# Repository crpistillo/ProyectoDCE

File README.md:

# ProyectoDCE

Los archivos correspondientes a la Primera entrega: TP1 - Etapa de control se encuentran en el directorio *PROYECTO_ETAPA_CONTROL*

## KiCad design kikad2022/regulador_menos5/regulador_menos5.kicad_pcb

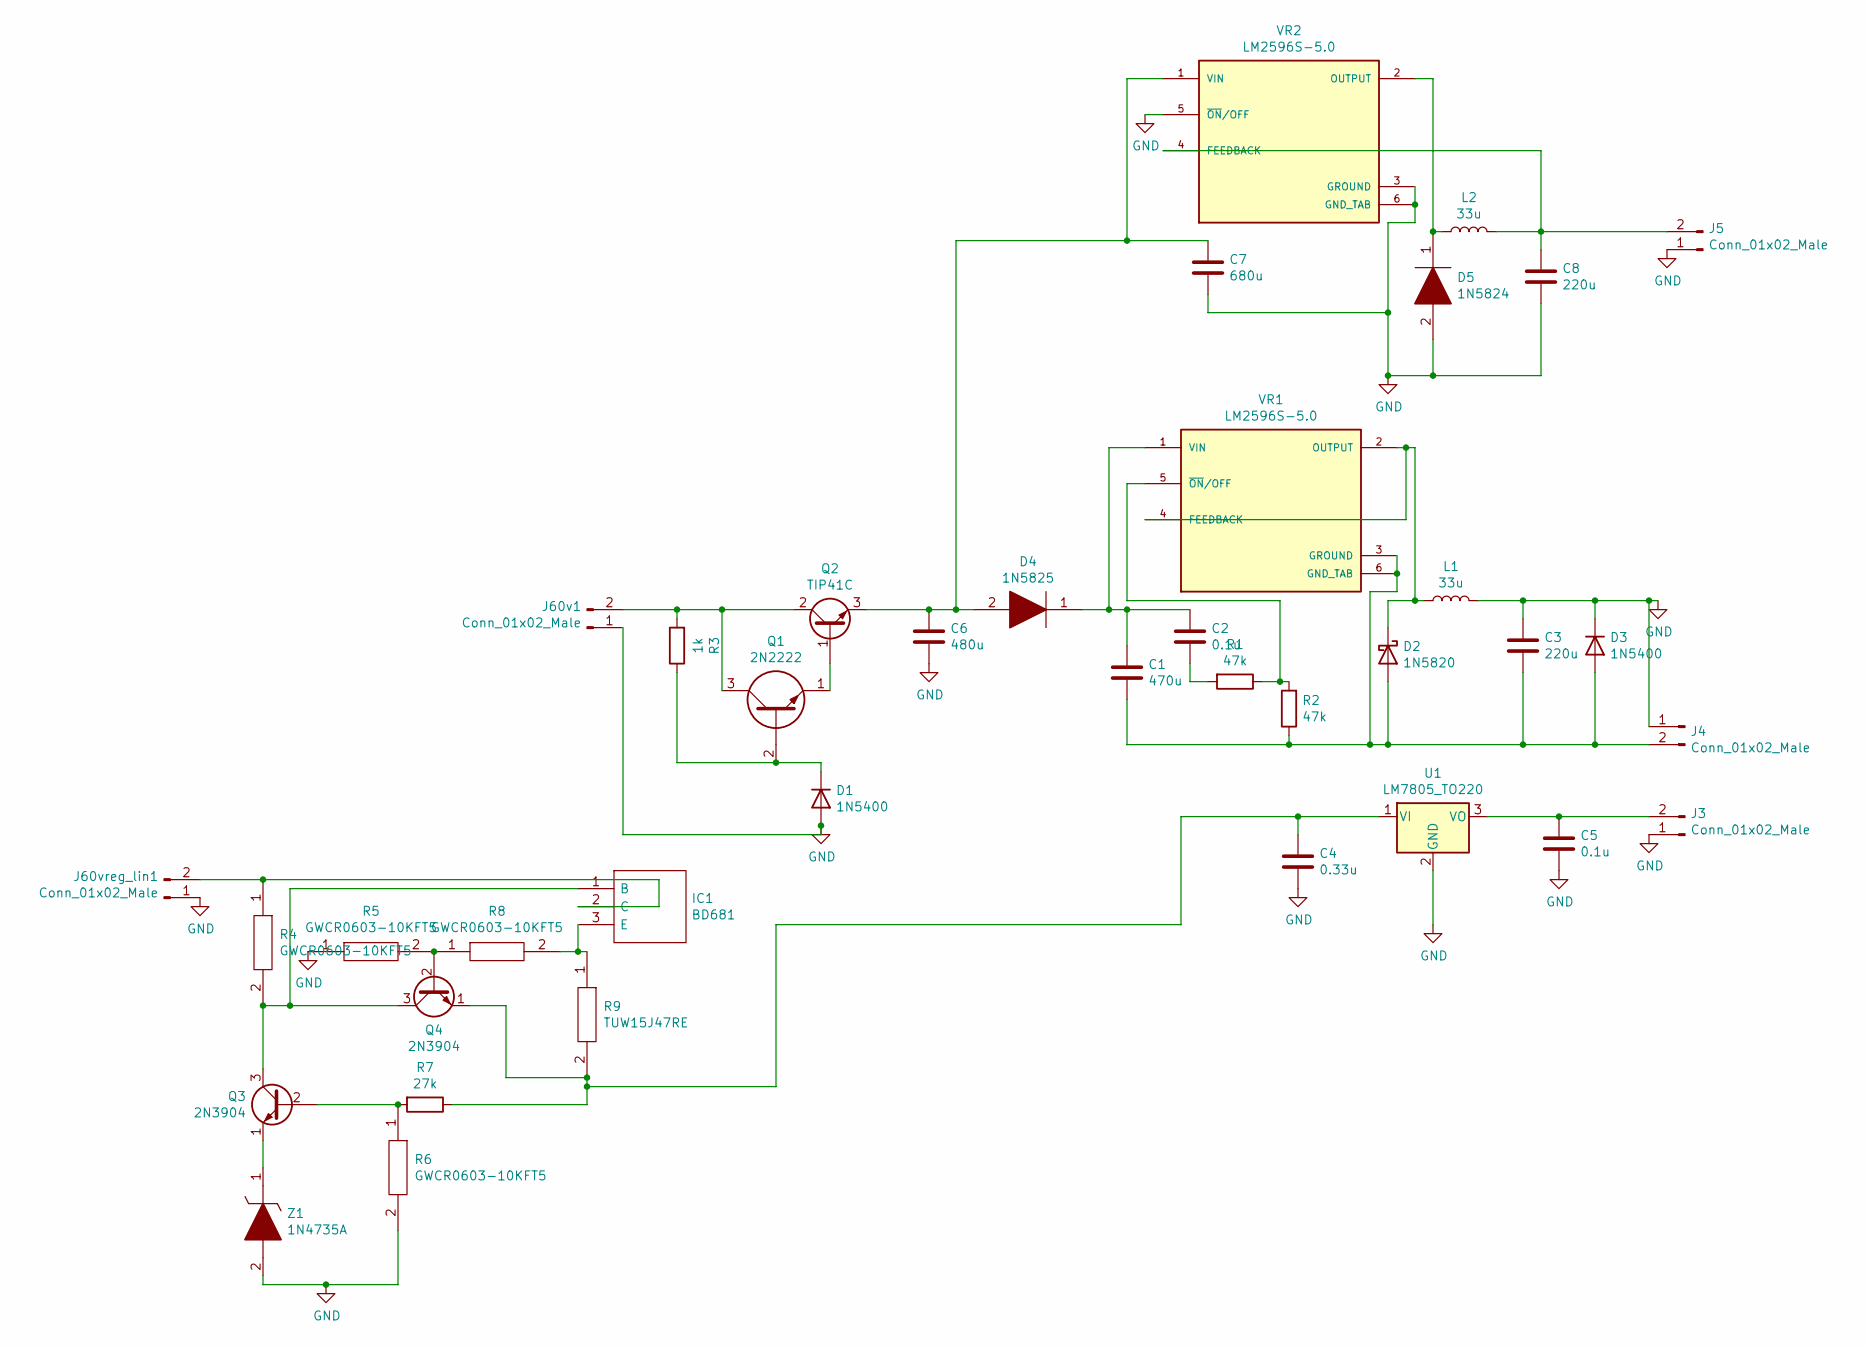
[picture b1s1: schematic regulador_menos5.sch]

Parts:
C1: 470u; CAPC2012X100N
C2, C5: 0.1u; CAPC2012X100N
C3, C8: 220u; CAPC2012X100N
C4: 0.33u; CAPC2012X100N
C6: 480u; CAPC2012X100N
C7: 680u; CAPC2012X100N
D1, D3: 1N5400; D_DO-201AD_P15.24mm_Horizontal
D2: 1N5820; D_DO-201AD_P15.24mm_Horizontal
D4: 1N5825; 1N5824; Manufacturer_Part_Number 1N5825; Mouser Part Number 494-1N5825
D5: 1N5824; Manufacturer_Part_Number 1N5824; Mouser Part Number 494-1N5824
IC1: BD681; TO254P290X760X1320-3P; Manufacturer_Part_Number BD681; Mouser Part Number 511-BD681
J3, J4, J5, J60v1, J60vreg_lin1: Conn_01x02_Male; Molex_KK-254_AE-6410-02A_1x02_P2.54mm_Vertical
L1, L2: 33u; L_TDK_NLV32_3.2x2.5mm
Q1: 2N2222; Manufacturer_Part_Number 2N2222
Q2: TIP41C; TO-220-3_Vertical
Q3, Q4: 2N3904; TO-92_Inline
R1, R2: 47k; R_0603_1608Metric
R3: 1k; R_0603_1608Metric
R4, R5, R6, R8: GWCR0603-10KFT5; RESC1608X55N; Manufacturer_Part_Number GWCR0603-10KFT5
R7: 27k; RESC1608X55N
R9: TUW15J47RE; TUW15J27RE; Manufacturer_Part_Number TUW15J47RE; Mouser Part Number 588-TUW15J47RE
U1: LM7805_TO220; TO-220-3_Vertical
VR1, VR2: LM2596S-5.0; KTT0005B; PARTREV E
Z1: 1N4735A; DIOAD1413W86L463D238; Manufacturer_Part_Number 1N4735A; Mouser Part Number 512-1N4735A

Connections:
GND: C3.1, C4.2, C5.2, C6.2, C7.2, C8.2, D1.2 (A), D3.1 (K), D5.2, J3.1, J4.1, J5.1, J60v1.1, J60vreg_lin1.1, L1.2, R5.1, R6.2, U1.2 (GND), VR2.3 (GROUND), VR2.5 (~ON~/OFF), VR2.6 (GND_TAB), Z1.2
unnamed: C1.1, C2.1, D4.1, VR1.1 (VIN)
unnamed: C1.2, C3.2, D2.2 (A), D3.2 (A), J4.2, R2.1, VR1.3 (GROUND), VR1.6 (GND_TAB)
unnamed: C2.2, R1.2
unnamed: C4.1, Q4.1 (E), R7.1, R9.2, U1.1 (VI)
unnamed: C5.1, J3.2, U1.3 (VO)
unnamed: C6.1, C7.1, D4.2, Q2.3 (E), VR2.1 (VIN)
unnamed: C8.1, J5.2, L2.2, VR2.4 (FEEDBACK)
unnamed: D1.1 (K), Q1.2, R3.1
unnamed: D2.1 (K), L1.1, VR1.2 (OUTPUT), VR1.4 (FEEDBACK)
unnamed: D5.1, L2.1, VR2.2 (OUTPUT)
unnamed: IC1.1 (B), Q3.3 (C), Q4.3 (C), R4.2
unnamed: IC1.2 (C), J60vreg_lin1.2, R4.1
unnamed: IC1.3 (E), R8.2, R9.1
unnamed: J60v1.2, Q1.3, Q2.2 (C), R3.2
unnamed: Q1.1, Q2.1 (B)
unnamed: Q3.1 (E), Z1.1
unnamed: Q3.2 (B), R6.1, R7.2
unnamed: Q4.2 (B), R5.2, R8.1
unnamed: R1.1, R2.2, VR1.5 (~ON~/OFF)

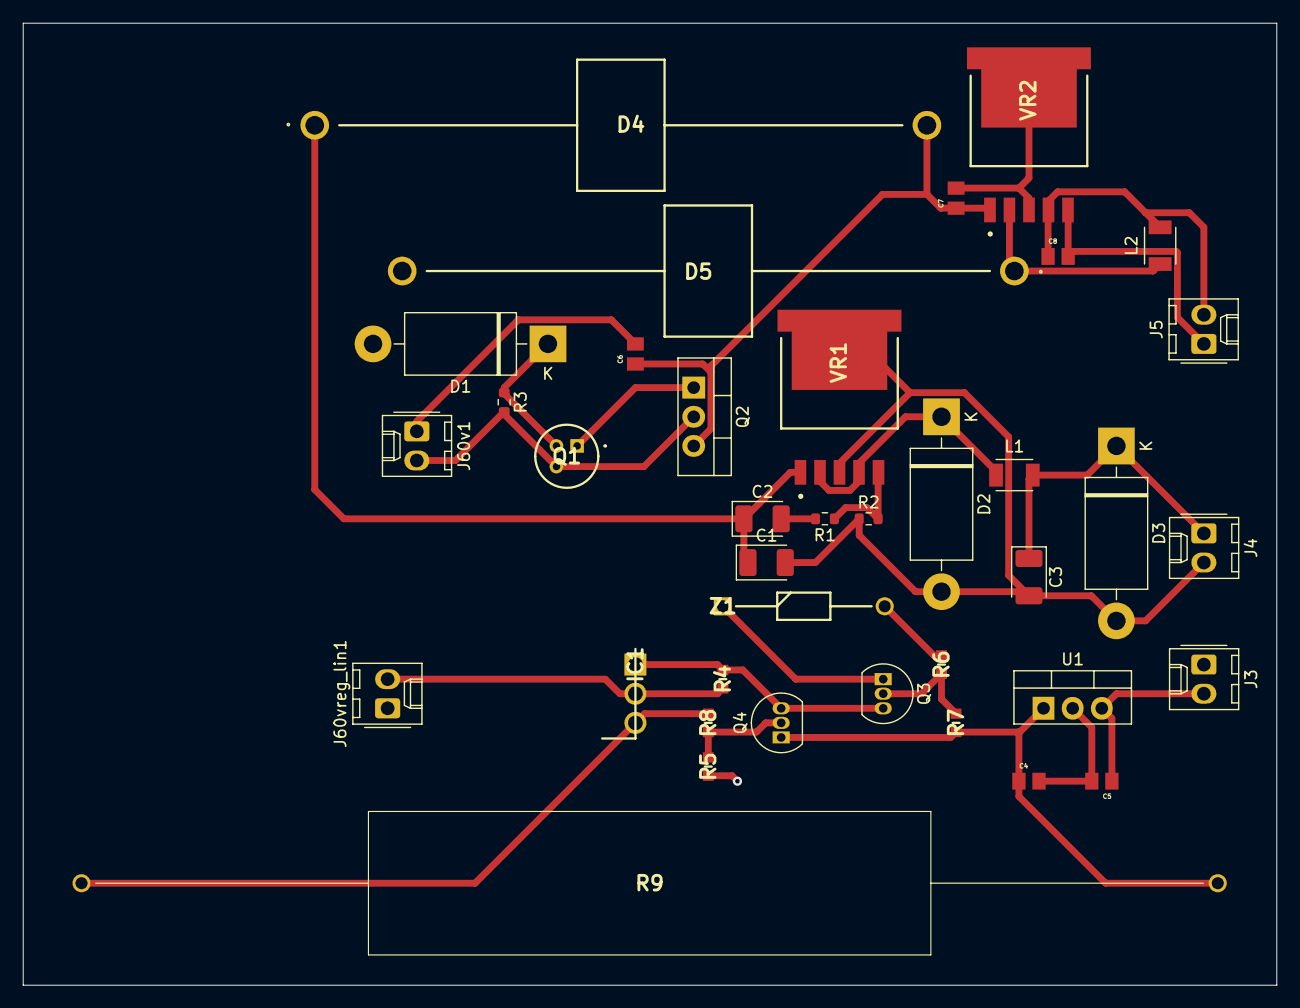
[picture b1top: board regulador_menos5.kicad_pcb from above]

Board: 2 copper layers, 109.2 x 83.8 mm, 38 parts (0 on the bottom side), 20 nets.

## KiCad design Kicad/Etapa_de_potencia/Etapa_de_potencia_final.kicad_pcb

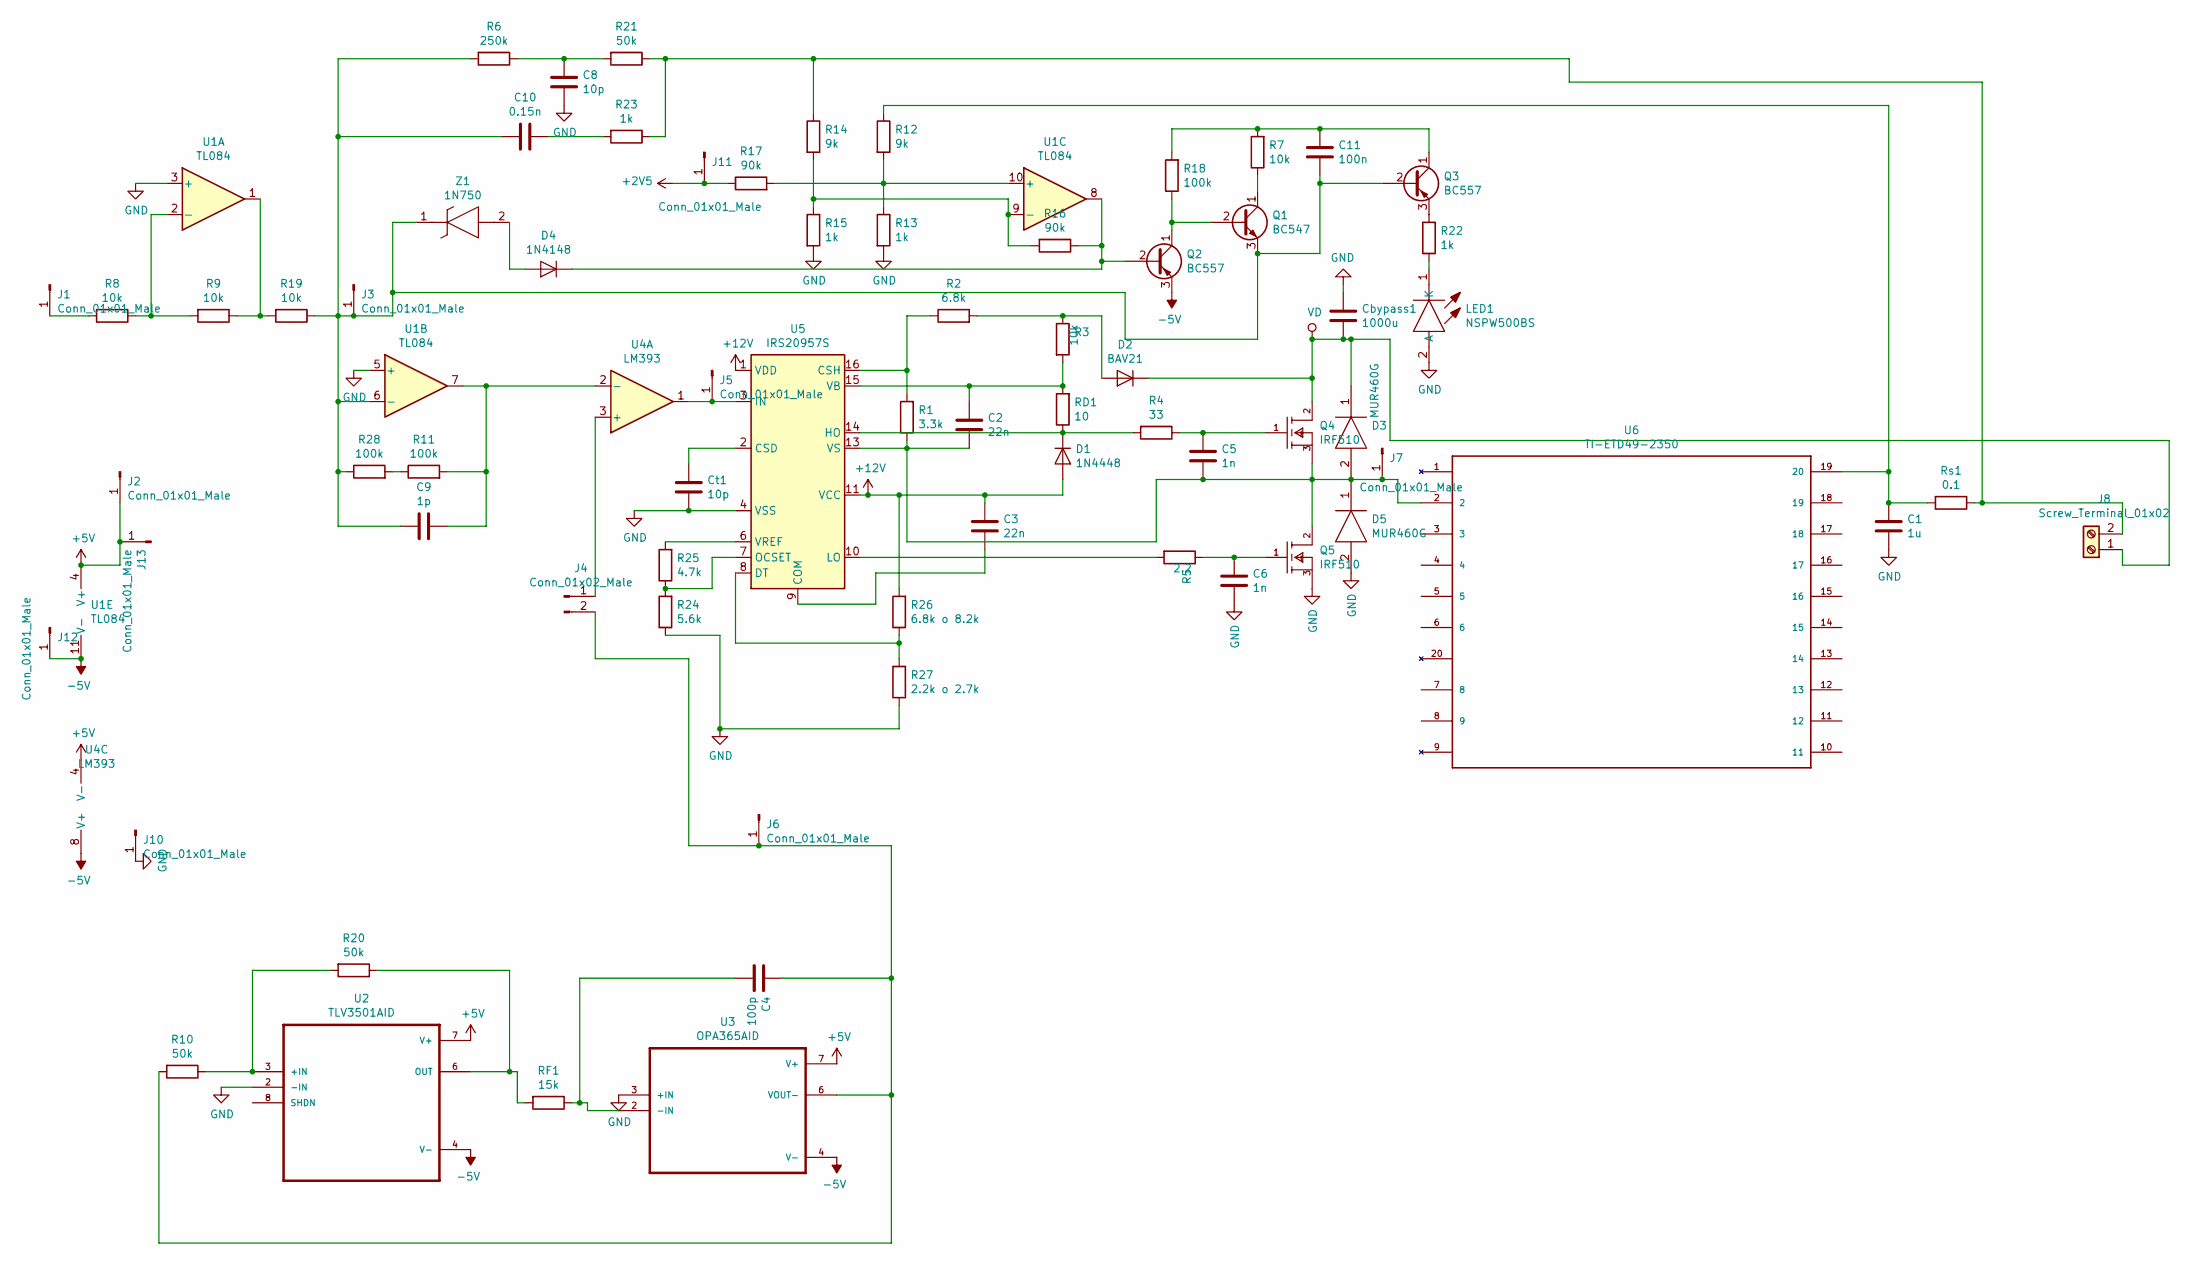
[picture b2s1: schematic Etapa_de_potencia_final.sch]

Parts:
C1: 1u; C_Radial_D5.0mm_H11.0mm_P2.00mm
C2, C3: 22n; C_1206_3216Metric
C4: 100p; C_1206_3216Metric
C5, C6: 1n; C_1206_3216Metric
C8: 10p; C_1206_3216Metric
C9: 1p; C_Disc_D8.0mm_W5.0mm_P5.00mm
C10: 0.15n; C_0805_2012Metric
C11: 100n; C_0603_1608Metric
Cbypass1: 1000u; C_Radial_D16.0mm_H25.0mm_P7.50mm
Ct1: 10p; C_1206_3216Metric
D1: 1N4448; D_DO-35_SOD27_P7.62mm_Horizontal
D2: BAV21; D_DO-35_SOD27_P7.62mm_Horizontal
D3, D5: MUR460G; DIOAD2860W130L840D505; Manufacturer_Part_Number MUR460G; Mouser Part Number 863-MUR460G
D4: 1N4148; D_DO-35_SOD27_P7.62mm_Horizontal
J1, J2, J3, J5, J6, J7, J10, J11, J12, J13: Conn_01x01_Male; PinHeader_1x01_P1.00mm_Vertical
J4: Conn_01x02_Male; PinHeader_1x02_P1.00mm_Vertical
J8: Screw_Terminal_01x02; TerminalBlock_bornier-2_P5.08mm
LED1: NSPW500BS; Manufacturer_Part_Number NSPW500BS
Q1: BC547; TO-92_Inline
Q2, Q3: BC557; TO-92_Inline
Q4, Q5: IRF510; Vishay-IRF510-0; mouser part number 844-IRF510; digikey description MOSFET N-CH 100V 5.6A TO-220AB
R1: 3.3k; R_0603_1608Metric
R2: 6.8k; R_0603_1608Metric
R3, R7, R8, R9, R19: 10k; R_0603_1608Metric
R4: 33; R_Axial_DIN0309_L9.0mm_D3.2mm_P2.54mm_Vertical
R5: 2.2; R_Axial_DIN0309_L9.0mm_D3.2mm_P2.54mm_Vertical
R6: 250k; R_0603_1608Metric
R10, R20, R21: 50k; R_0603_1608Metric
R11, R18, R28: 100k; R_0603_1608Metric
R12, R14: 9k; R_0603_1608Metric
R13, R15, R22, R23: 1k; R_0603_1608Metric
R16, R17: 90k; R_0603_1608Metric
R24: 5.6k; R_0603_1608Metric
R25: 4.7k; R_0603_1608Metric
R26: 6.8k o 8.2k; R_0603_1608Metric
R27: 2.2k o 2.7k; R_0603_1608Metric
RD1: 10; R_0603_1608Metric
RF1: 15k; R_0603_1608Metric
Rs1: 0.1; R_0603_1608Metric
U1: TL084; SOIC-14_3.9x8.7mm_P1.27mm
U2: TLV3501AID; SOIC127P599X175-8N
U3: OPA365AID; SOIC127P599X175-8N
U4: LM393; SOIC-8_3.9x4.9mm_P1.27mm
U5: IRS20957S; SOIC-16_3.9x9.9mm_P1.27mm
U6: TI-ETD49-2350; ETD49-K-H-20P
Z1: 1N750; DIOAD1256W56L444D203; Manufacturer_Part_Number 1N750; Mouser Part Number 494-1N750(DO-35)

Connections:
+2V5: J11.1, R17.1
+5V: J2.1, J13.1, U1.4 (V+), U2.7 (V+), U3.7 (V+), U4.4 (V-)
+12V: C3.2, D1.2 (A), R26.2, U5.1 (VDD), U5.11 (VCC)
-5V: J12.1, Q2.3 (E), U1.11 (V-), U2.4 (V-), U3.4 (V-), U4.8 (V+)
GND: C1.2, C6.2, C8.1, Cbypass1.2, Ct1.1, D5.2, J10.1, LED1.2 (A), Q5.3 (S), R13.2, R15.2, R24.1, R27.1, U1.3 (+), U1.5 (+), U2.2 (-IN), U3.3 (+IN), U5.4 (VSS)
unnamed: C1.1, R12.1, Rs1.2, U6.19 (20)
unnamed: C2.1, C5.2, D3.2, D5.1, J7.1, Q4.3 (S), Q5.2 (D), R1.1, U5.13 (VS), U6.2
unnamed: C2.2, R3.2, RD1.2, U5.15 (VB)
unnamed: C3.1, U5.9 (COM)
unnamed: C4.1, RF1.1, U3.2 (-IN)
unnamed: C4.2, J4.2, J6.1, R10.2, U3.6 (VOUT-)
unnamed: C5.1, Q4.1 (G), R4.1
unnamed: C6.1, Q5.1 (G), R5.1
unnamed: C8.2, R6.1, R21.2
unnamed: C9.1, R11.2, U1.7, U4.2 (-)
unnamed: C9.2, C10.1, C11.1, J3.1, Q1.3 (E), Q3.2 (B), R6.2, R19.1, R28.1, U1.6 (-), Z1.1
unnamed: C10.2, R23.2
unnamed: C11.2, Q3.1 (C), R7.2, R18.2
unnamed: Ct1.2, U5.2 (CSD)
unnamed: D1.1 (K), R4.2, RD1.1, U5.14 (HO)
unnamed: D2.2 (A), R2.2, R3.1
unnamed: D4.1 (K), Q2.2 (B), R16.1, U1.8
unnamed: D4.2 (A), Z1.2
unnamed: J1.1, R8.2
unnamed: J4.1, U4.3 (+)
unnamed: J5.1, U4.1, U5.3 (IN)
unnamed: J8.2, R14.1, R21.1, R23.1, Rs1.1
unnamed: LED1.1 (K), R22.1
unnamed: Q1.1 (C), R7.1
unnamed: Q1.2 (B), Q2.1 (C), R18.1
unnamed: Q3.3 (E), R22.2
unnamed: R1.2, R2.1, U5.16 (CSH)
unnamed: R5.2, U5.10 (LO)
unnamed: R8.1, R9.2, U1.2 (-)
unnamed: R10.1, R20.2, U2.3 (+IN)
unnamed: R11.1, R28.2
unnamed: R12.2, R13.1, R17.2, U1.10 (+)
unnamed: R14.2, R15.1, R16.2, U1.9 (-)
unnamed: R9.1, R19.2, U1.1
unnamed: R20.1, RF1.2, U2.6 (OUT)
unnamed: R24.2, R25.1, U5.7 (OCSET)
unnamed: R25.2, U5.6 (VREF)
unnamed: R26.1, R27.2, U5.8 (DT)
VD: Cbypass1.1, D2.1 (K), D3.1, J8.1, Q4.2 (D)

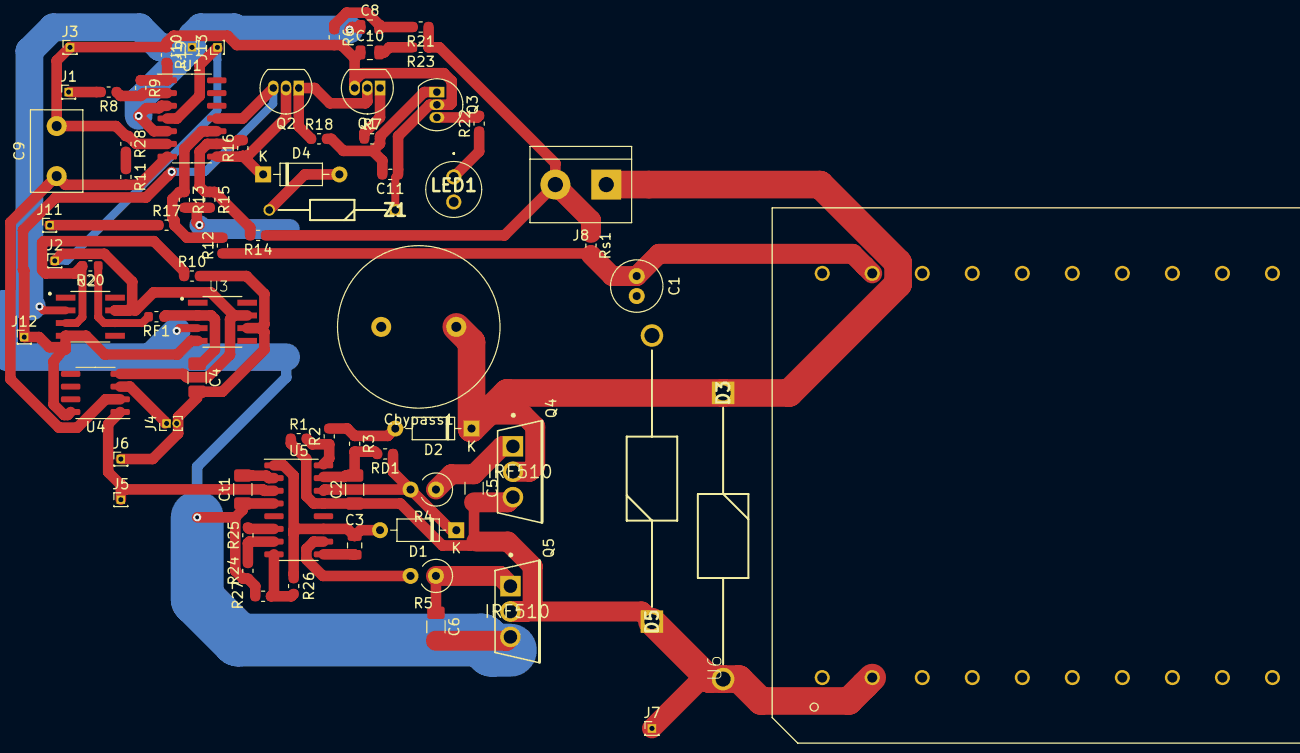
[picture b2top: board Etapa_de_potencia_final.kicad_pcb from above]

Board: 2 copper layers, 73 parts (0 on the bottom side), 44 nets.

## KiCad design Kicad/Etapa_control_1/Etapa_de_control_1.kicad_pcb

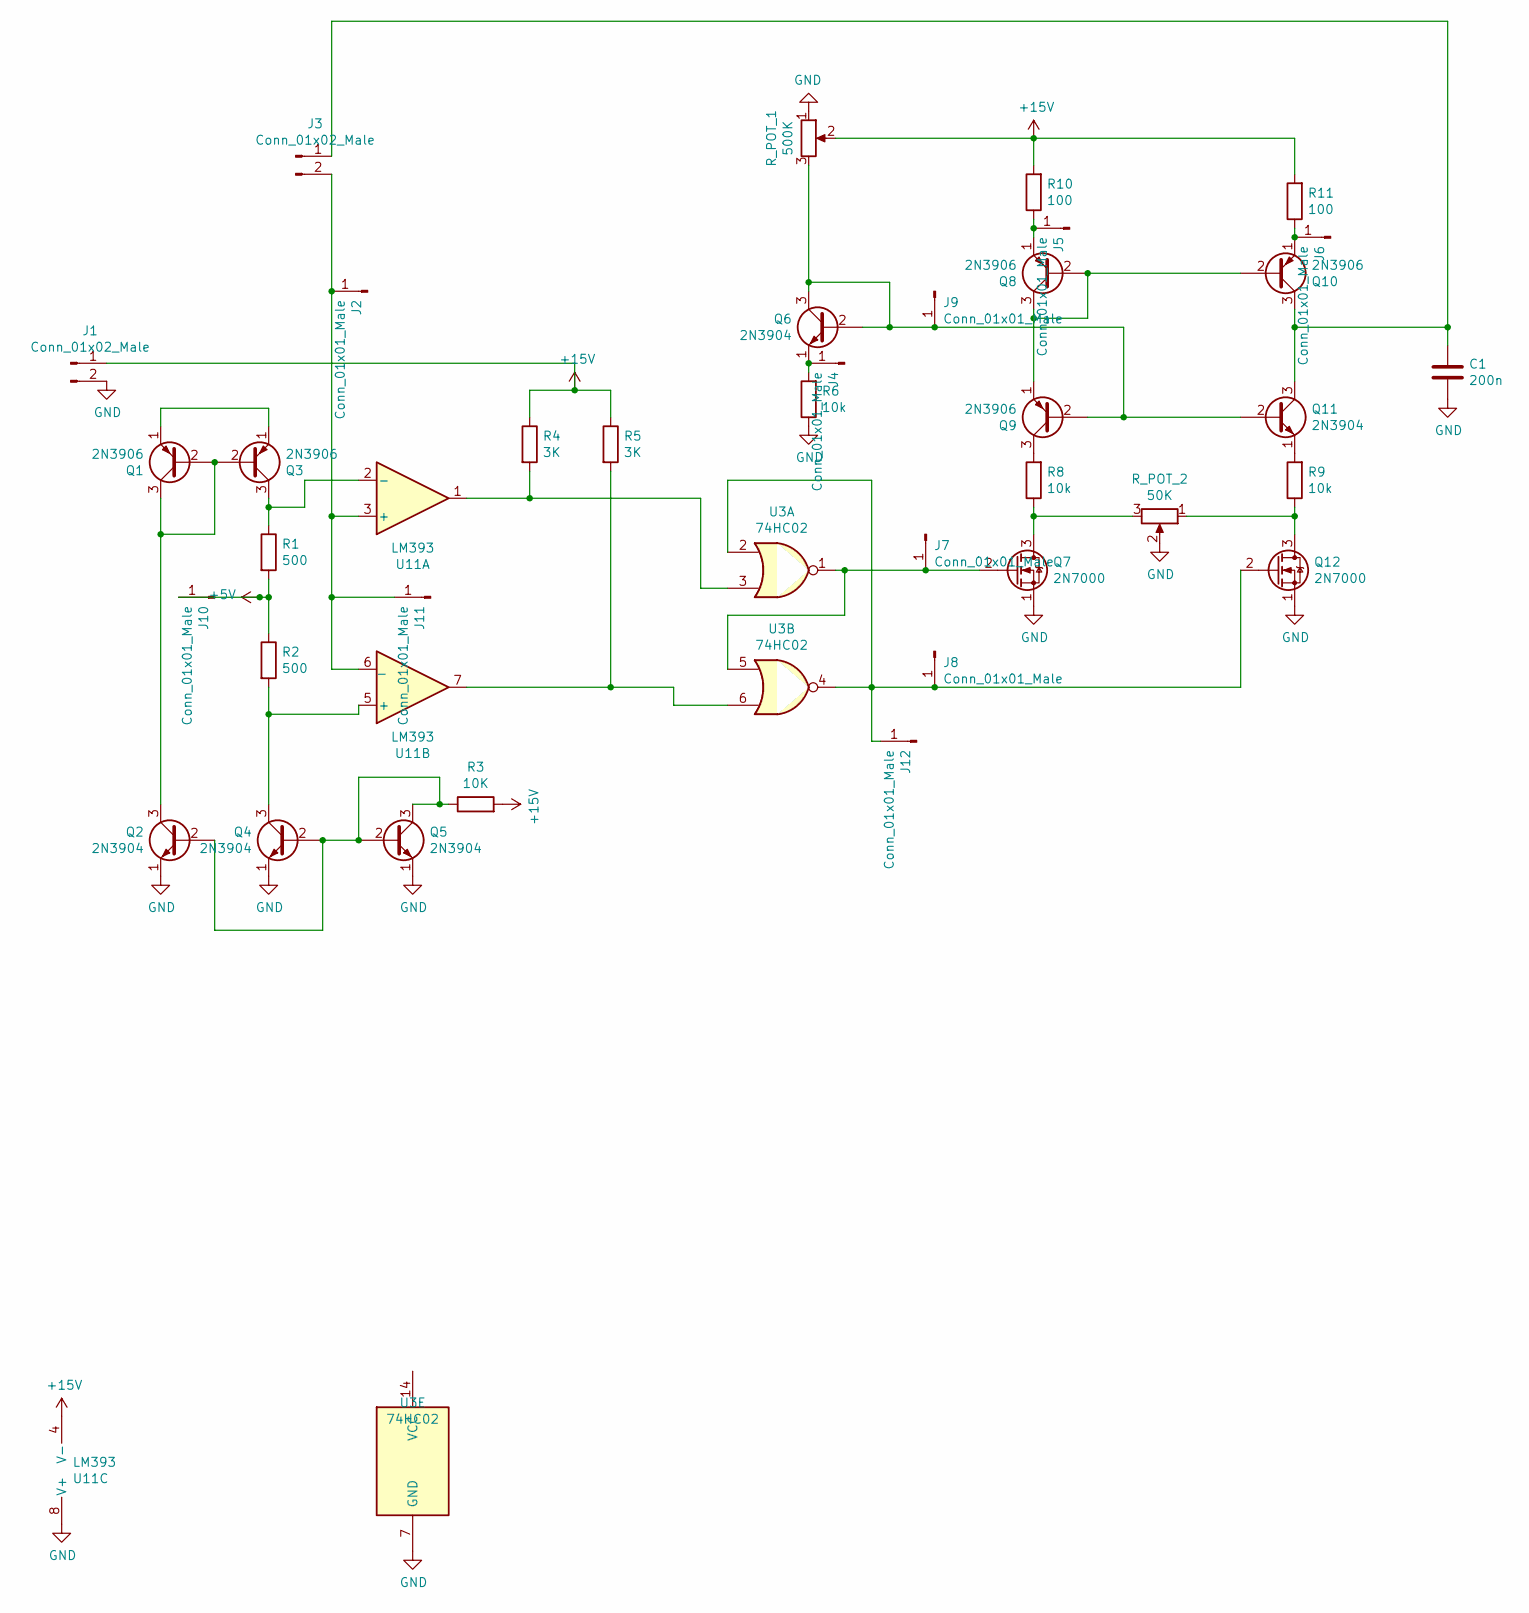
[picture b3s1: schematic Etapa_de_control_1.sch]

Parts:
C1: 200n; C_Disc_D3.8mm_W2.6mm_P2.50mm
J1, J3: Conn_01x02_Male; PinHeader_1x02_P1.00mm_Vertical
J2, J4, J5, J6, J7, J8, J9, J10, J11, J12: Conn_01x01_Male; PinHeader_1x01_P1.00mm_Vertical
Q1, Q3, Q8, Q9, Q10: 2N3906; TO-92_Inline
Q2, Q4, Q5, Q6, Q11: 2N3904; TO-92_Inline
Q7, Q12: 2N7000; TO-92_Inline
R1, R2: 500; R_0603_1608Metric
R3: 10K; R_0603_1608Metric
R4, R5: 3K; R_0603_1608Metric
R6, R8, R9: 10k; R_0603_1608Metric
R10, R11: 100; R_0603_1608Metric
R_POT_1: 500K; Potentiometer_Bourns_3296W_Vertical
R_POT_2: 50K; Potentiometer_Bourns_3296W_Vertical
U3: 74HC02; DIP-14_W7.62mm
U11: LM393; DIP-8_W7.62mm

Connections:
+5V: J10.1, R1.2, R2.1
+15V: J1.1, R3.2, R4.1, R5.1, R10.2, R11.2, R_POT_1.2, U11.4 (V-)
GND: C1.2, J1.2, Q2.1 (E), Q4.1 (E), Q5.1 (E), Q7.1 (S), Q12.1 (S), R6.1, R_POT_1.1, R_POT_2.2, U3.7 (GND), U11.8 (V+)
unnamed: C1.1, J3.1, Q10.3 (C), Q11.3 (C)
unnamed: J4.1, Q6.1 (E), R6.2
unnamed: J5.1, Q8.1 (E), R10.1
unnamed: J6.1, Q10.1 (E), R11.1
unnamed: J7.1, Q7.2 (G), U3.1, U3.5
unnamed: J9.1, Q6.2 (B), Q6.3 (C), Q9.2 (B), Q11.2 (B), R_POT_1.3
unnamed: J2.1, J3.2, J11.1, U11.3 (+), U11.6 (_)
unnamed: J8.1, J12.1, Q12.2 (G), U3.2, U3.4
unnamed: Q1.1 (E), Q3.1 (E)
unnamed: Q1.2 (B), Q1.3 (C), Q2.3 (C), Q3.2 (B)
unnamed: Q2.2 (B), Q4.2 (B), Q5.2 (B), Q5.3 (C), R3.1
unnamed: Q3.3 (C), R1.1, U11.2 (-)
unnamed: Q4.3 (C), R2.2, U11.5 (+)
unnamed: Q7.3 (D), R8.1, R_POT_2.3
unnamed: Q9.3 (C), R8.2
unnamed: Q8.2 (B), Q8.3 (C), Q9.1 (E), Q10.2 (B)
unnamed: Q11.1 (E), R9.2
unnamed: Q12.3 (D), R9.1, R_POT_2.1
unnamed: R4.2, U3.3, U11.1
unnamed: R5.2, U3.6, U11.7

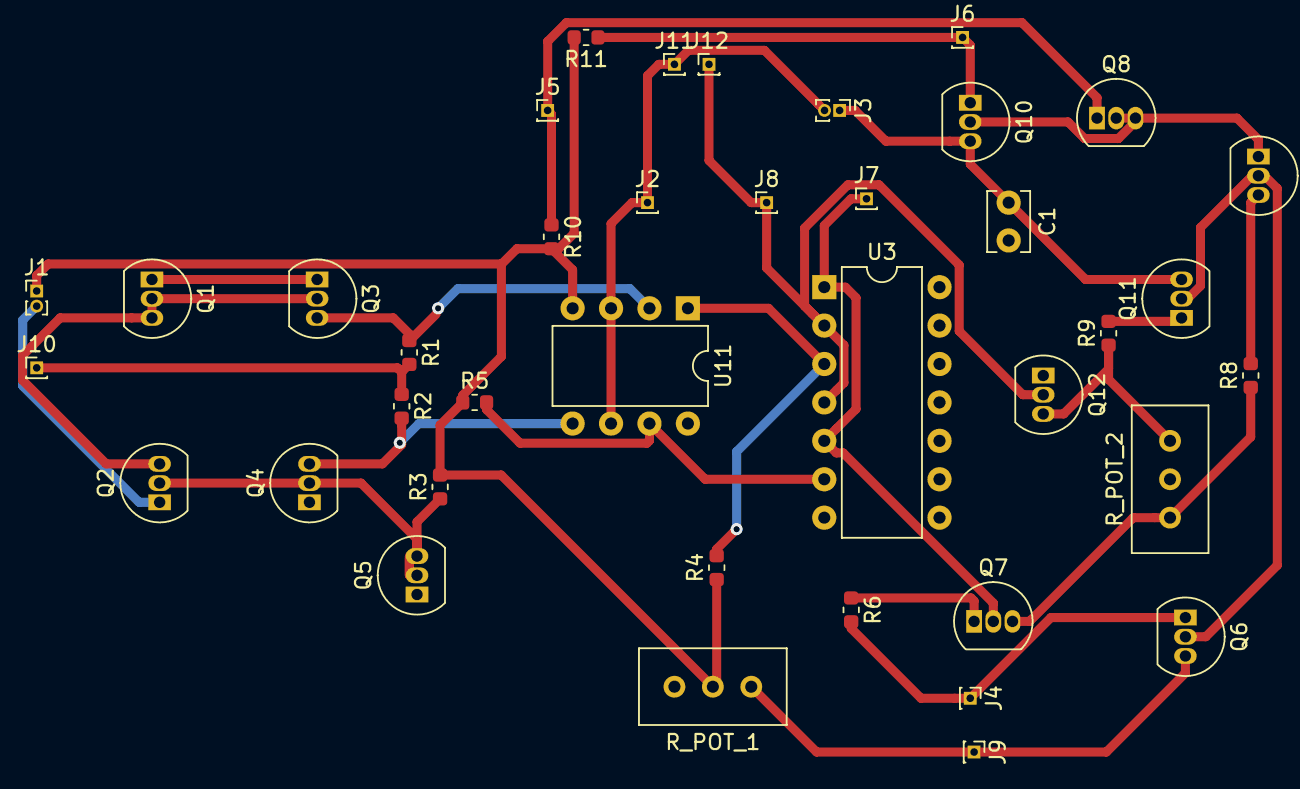
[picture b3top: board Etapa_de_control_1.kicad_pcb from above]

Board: 2 copper layers, 39 parts (0 on the bottom side), 23 nets.

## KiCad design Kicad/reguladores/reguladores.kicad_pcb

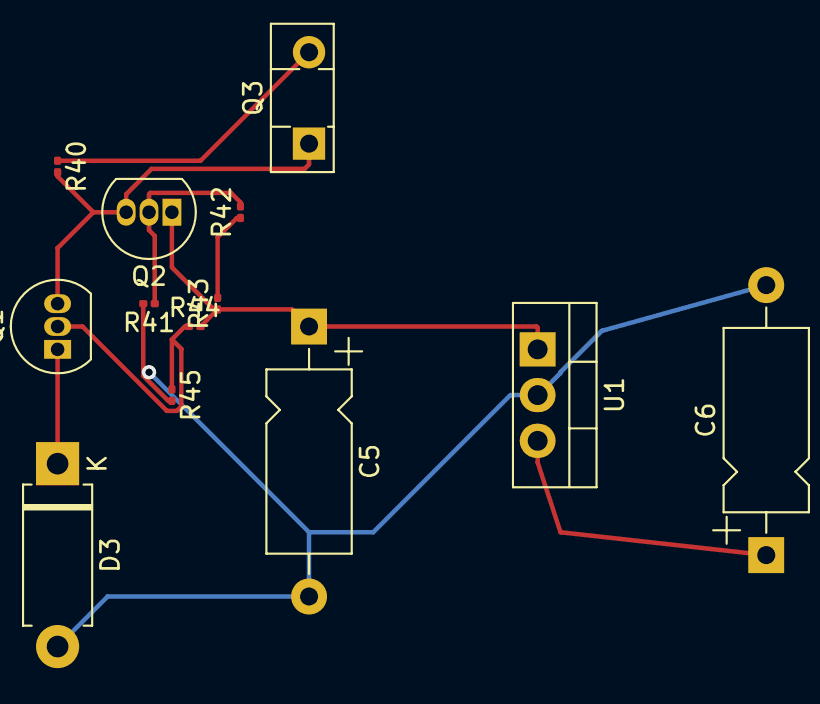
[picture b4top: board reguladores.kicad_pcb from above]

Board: 2 copper layers, 13 parts (0 on the bottom side), 9 nets.

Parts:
C5, C6: 100n; CP_Axial_L10.0mm_D4.5mm_P15.00mm_Horizontal
D3: 1N47xxA; D_DO-15_P10.16mm_Horizontal
Q1, Q2: 2N3904; TO-92_Inline
Q3: Q_NPN_Darlington_BCE; TO-126-2_Vertical
R40, R45: 10K; R_0201_0603Metric
R41, R42: 2K; R_0201_0603Metric
R43: 26; R_0201_0603Metric
R44: 27K; R_0201_0603Metric
U1: LM7815_TO220; TO-220-3_Vertical

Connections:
GND: C5.2, C6.2, D3.2, R41.2, R45.2, U1.2
unnamed: C5.1, Q2.1, R43.1, R44.2, U1.1
unnamed: C6.1, U1.3
unnamed: D3.1, Q1.1
unnamed: Q1.2, R44.1, R45.1
unnamed: Q1.3, Q2.3, Q3.1, R40.2
unnamed: Q2.2, R41.1, R42.2
unnamed: R42.1, R43.2
VCC: Q3.2, R40.1

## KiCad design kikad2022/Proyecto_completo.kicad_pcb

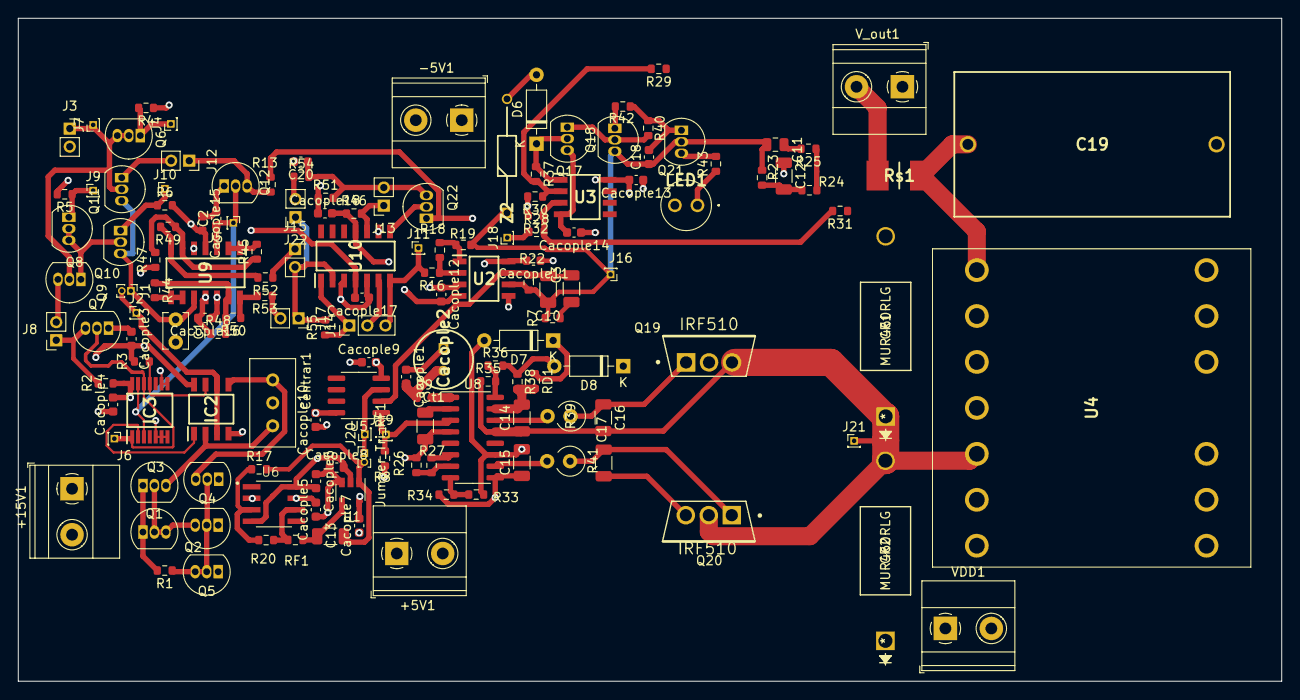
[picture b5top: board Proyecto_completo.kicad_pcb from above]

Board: 4 copper layers, 139.7 x 73.3 mm, 150 parts (0 on the bottom side), 79 nets.

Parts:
+5V1: +5; TerminalBlock_Phoenix_MKDS-1,5-2-5.08_1x02_P5.08mm_Horizont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
+15V1: +15; TerminalBlock_Phoenix_MKDS-1,5-2-5.08_1x02_P5.08mm_Horizont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
-5V1: -5; TerminalBlock_Phoenix_MKDS-1,5-2-5.08_1x02_P5.08mm_Horizont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
C1: 200n; C_Disc_D3.8mm_W2.6mm_P2.50mm
C2: 0.1u; C_0603_1608Metric
C3, C10: 1p; C_1206_3216Metric
C11: 0.15n; C_0805_2012Metric
C12: 10p; C_1206_3216Metric
C13: 100p; C_1206_3216Metric
C14, C15: 22n; C_1206_3216Metric
C16, C17: 1n; C_1206_3216Metric
C18: 100n; C_0603_1608Metric
C19: 1u; 158X105
C20: 0.01u; C_0603_1608Metric
CR1, CR2: MUR460RLG
Cacople1, Cacople3, Cacople5, Cacople6, Cacople7, Cacople8, Cacople15, Cacople16, Cacople17, Cacople18: 100n; C_0603_1608Metric
Cacople2: 100u; CAPPRD250W50D655H1250
Cacople4, Cacople9, Cacople10, Cacople11, Cacople12, Cacople13, Cacople14: 10p; C_0603_1608Metric
Centrar1: 500; Potentiometer_Bourns_3296W_Vertical
Ct1: 10p; C_1206_3216Metric
D6: 1N4148; D_DO-35_SOD27_P7.62mm_Horizontal
D7: 1N4448; D_DO-35_SOD27_P7.62mm_Horizontal
D8: BAV21; D_DO-35_SOD27_P7.62mm_Horizontal
IC2: LM393AD; SOIC127P600X175-8N
IC3: 74HC02PW,112; SOP65P640X110-14N
J1: Conn_01x02_Male; PinHeader_1x02_P1.00mm_Vertical
J2, J4, J5, J6, J7, J9, J10, J11, J18: Conn_01x01_Male; PinHeader_1x01_P1.00mm_Vertical
J3: Pot_frec; PinSocket_1x02_P2.00mm_Vertical
J8, J12: Pot_paralelo; PinSocket_1x02_P2.00mm_Vertical
J13: DC_amplitud; PinSocket_1x02_P2.00mm_Vertical
J14: Amplitud; PinHeader_1x03_P2.00mm_Vertical
J15: Swich_triang; PinSocket_1x02_P2.00mm_Vertical
J16: Realimentacion; PinHeader_1x01_P1.00mm_Vertical
J17: Swich_Cua; PinSocket_1x02_P2.00mm_Vertical
J19: V_in_Driver; PinHeader_1x01_P1.00mm_Vertical
J20: V_Triang_RF; PinHeader_1x01_P1.00mm_Vertical
J21: L; PinHeader_1x01_P1.00mm_Vertical
J22: swich_DC; PinSocket_1x02_P2.00mm_Vertical
Jumper_Tri_RF1: Jumper_Tri_RF; PinHeader_1x02_P1.00mm_Vertical
LED1: NSPW500BS
Q1, Q3, Q8, Q9, Q10: 2N3906; TO-92_Inline
Q2, Q4, Q5, Q6, Q11: 2N3904; TO-92_Inline
Q7, Q12: 2N7000; TO-92_Inline
Q17, Q21: BC557; TO-92_Inline
Q18: BC547; TO-92_Inline
Q19, Q20: IRF510; Vishay-IRF510-0
Q22: Q_PMOS_DGS; TO-92_Inline
R1, R2, R13: 10K; R_0603_1608Metric
R3: 3K; R_0603_1608Metric
R4, R16, R18, R19, R38, R42, R44, R51, R52, R53, R54, R55: 10k; R_0603_1608Metric
R5, R6: 100; R_0603_1608Metric
R7, R22, R40: 100k; R_0603_1608Metric
R8: 3k; R_0603_1608Metric
R9: 2.2k; R_0603_1608Metric
R17, R20, R24: 50k; R_0603_1608Metric
R23: 250k; R_0603_1608Metric
R25, R30, R32, R43: 1k; R_0603_1608Metric
R26: 4.7k; R_0603_1608Metric
R27: 5.6k; R_0603_1608Metric
R28, R37: 90k; R_0603_1608Metric
R29, R31: 9k; R_0603_1608Metric
R33: 6.8k o 8.2k; R_0603_1608Metric
R34: 2.2k o 2.7k; R_0603_1608Metric
R35: 3.3k; R_0603_1608Metric
R36, R50: 6.8k; R_0603_1608Metric
R39: 33; R_Axial_DIN0309_L9.0mm_D3.2mm_P2.54mm_Vertical
R41: 2.2; R_Axial_DIN0309_L9.0mm_D3.2mm_P2.54mm_Vertical
R45: 20k; R_0603_1608Metric
R46: R; R_0603_1608Metric
R47, R48: 40k; R_0603_1608Metric
R49: 3.9k; R_0603_1608Metric
RD1: 10; R_0603_1608Metric
RF1: 15k; R_0603_1608Metric
Rs1: 0.1; RESC6331X80N
U1: OPA365xxDBV; SOT-23-5
U2, U3: TL082; SOIC127P600X175-8N
U4: CPH-ETD29-1S-13P; CPHETD291S13P
U5: LM393; SOIC-8_3.9x4.9mm_P1.27mm
U6: TLV3501AID; SOIC127P599X175-8N
U8: IRS20957S; SOIC-16_3.9x9.9mm_P1.27mm
U9, U10: TL084; SOIC127P600X175-14N
VDD1: VD; TerminalBlock_Phoenix_MKDS-1,5-2-5.08_1x02_P5.08mm_Horizont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
V_out1: V_out; TerminalBlock_Phoenix_MKDS-1,5-2-5.08_1x02_P5.08mm_Horizont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
Z2: 1N750; DIOAD1256W56L444D203

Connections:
+2V5: J18.1, R28.1
+5V: +5V1.1, Cacople4.2, Cacople5.2, Cacople7.2, Cacople9.2, Cacople11.2, Cacople13.2, Centrar1.2, IC3.14, Q22.1, R2.2, R8.2, R13.1, U1.5, U2.8, U3.8, U5.4, U6.7
+15V: +15V1.1, C15.2, Cacople3.2, Cacople15.2, Cacople17.2, D7.2, IC2.8, J3.2, Q1.1, Q3.1, R1.2, R3.1, R5.2, R6.2, R33.2, U8.11, U9.4, U10.4
-5V: -5V1.2, Cacople6.2, Cacople8.2, Cacople10.2, Cacople12.2, Cacople14.2, Cacople16.2, Cacople18.2, Q17.3, R46.1, R47.1, R48.1, U1.2, U2.4, U3.4, U5.8, U6.4, U6.8, U9.11, U10.11
/control2/Vo_control: J11.1, J14.3, R16.2, U10.7
/control/OUT_Capacitor: C1.1, J1.1, Q10.3, Q11.3, U9.10
/control/V_flipflop: C2.1, IC3.3, IC3.13, J5.1, Q12.2, U9.3
/potencia/V_Out: R24.1, R25.1, R29.1, Rs1.1, V_out1.2
GND: +5V1.2, +15V1.2, -5V1.1, C1.2, C2.2, C12.1, C15.1, C17.2, C19.2, C20.2, CR2.1, Cacople1.1, Cacople2.1, Cacople3.1, Cacople4.1, Cacople5.1, Cacople6.1, Cacople7.1, Cacople8.1, Cacople9.1, Cacople10.1, Cacople11.1, Cacople12.1, Cacople13.1, Cacople14.1, Cacople15.1, Cacople16.1, Cacople17.1, Cacople18.1, Ct1.1, IC2.4, IC3.5, IC3.6, IC3.7, IC3.8, IC3.9, LED1.2, Q2.1, Q4.1, Q5.1, Q7.1, Q12.1, Q20.3, R4.1, R27.1, R30.2, R32.2, R34.1, R51.1, U1.3, U2.3, U2.5, U6.2, U8.4, U8.9, U9.5, U9.12, U10.3, U10.5, U10.9, VDD1.2, V_out1.1
unnamed: C3.2, R7.2
unnamed: C3.1, C10.1, R22.2, U2.7, U5.2
unnamed: C10.2, C11.1, C18.1, J16.1, Q18.3, Q21.2, R7.1, R19.1, R22.1, R23.2, U2.6, Z2.1
unnamed: C11.2, R25.2
unnamed: C12.2, R23.1, R24.2
unnamed: C13.1, RF1.1, U1.4
unnamed: C13.2, Jumper_Tri_RF1.2, R17.2, U1.1
unnamed: C14.1, C16.2, CR1.1, CR2.2, J21.1, Q19.3, Q20.2, R35.1, U4.12, U8.13
unnamed: C14.2, R38.2, RD1.2, U8.15
unnamed: C16.1, Q19.1, R39.1
unnamed: C17.1, Q20.1, R41.1
unnamed: C18.2, Q21.1, R40.2, R42.2
unnamed: C19.1, R31.1, Rs1.2, U4.8
unnamed: C20.1, J13.2, Q22.3, R51.2, R54.2
unnamed: Centrar1.1, IC2.2, Q3.3
unnamed: Centrar1.3, IC2.5, Q4.3
unnamed: Ct1.2, U8.2
unnamed: D6.1, Q17.2, R37.1, U3.1
unnamed: D6.2, Z2.2
unnamed: D7.1, RD1.1
unnamed: D8.2, R36.2, R38.1
unnamed: IC2.1, IC3.2
unnamed: IC2.3, IC2.6, J1.2, J2.1
unnamed: IC2.7, IC3.11, R3.2
unnamed: IC3.1, IC3.12, J6.1, Q7.2
unnamed: J3.1, J7.1, Q6.2, Q6.3, Q9.2, Q11.2
unnamed: J4.1, Q6.1, R4.2
unnamed: J8.1, Q7.3, R2.1
unnamed: J8.2, Q9.3
unnamed: J9.1, Q8.1, R5.1
unnamed: J10.1, Q10.1, R6.1
unnamed: J12.1, Q12.3, R13.2
unnamed: J12.2, Q11.1
unnamed: J13.1, R46.2, U10.10
unnamed: J14.1, R55.1, U10.1
unnamed: J14.2, U10.6
unnamed: J15.1, R52.1
unnamed: J15.2, J17.1, J22.1, R55.2, U10.2
unnamed: J17.2, R53.1
unnamed: J19.1, R8.1, U5.1, U8.3
unnamed: J20.1, Jumper_Tri_RF1.1, U5.3
unnamed: J22.2, R54.1
unnamed: LED1.1, R43.1
unnamed: Q1.2, Q1.3, Q2.3, Q3.2
unnamed: Q2.2, Q4.2, Q5.2, Q5.3, R1.1
unnamed: Q8.2, Q8.3, Q9.1, Q10.2
unnamed: Q17.1, Q18.2, R40.1
unnamed: Q18.1, R42.1
unnamed: Q21.3, R43.2
unnamed: Q22.2, U10.8
unnamed: R9.2, U8.1
unnamed: R16.1, R18.2, U2.2
unnamed: R17.1, R20.2, U6.3
unnamed: R18.1, R19.2, U2.1
unnamed: R20.1, RF1.2, U6.6
unnamed: R26.1, R27.2, U8.7
unnamed: R26.2, U8.6
unnamed: R28.2, R31.2, R32.1, U3.3
unnamed: R29.2, R30.1, R37.2, U3.2
unnamed: R33.1, R34.2, U8.8
unnamed: R35.2, R36.1, U8.16
unnamed: R39.2, U8.14
unnamed: R41.2, U8.10
unnamed: R44.1, R48.2, R50.2, U9.13
unnamed: R44.2, U9.8, U9.9
unnamed: R45.1, R47.2, R49.1, U9.6
unnamed: R45.2, U9.1, U9.2
unnamed: R49.2, R52.2, U9.7
unnamed: R50.1, R53.2, U9.14
VD: CR1.2, Cacople1.2, Cacople2.2, D8.1, Q19.2, R9.1, VDD1.1

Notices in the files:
parts and their libraries:
Copyright 2016 Accelerated Designs. All rights reserved.
